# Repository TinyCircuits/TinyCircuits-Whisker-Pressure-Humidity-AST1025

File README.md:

# TinyCircuits Wireling Pressure Humidity
# AST1025 Rev2

The design files are located under design_files/ for the TinyCircuits AST1025 Rev 2 PCB. This is a Wireling board which features the Bosch BME280 Humidity, Pressure and Temperature Sensor all in one package! It measures between -40 and +85C, 0%-100% relative humidity, and from 300-1100hPa.

Format is in Cadsoft Eagle format - Eagle version 6.2 was used for the original design.

For more infomation on this, check out the product page at TinyCircuits.com

# License:

Design by TinyCircuits.
All design files are released under the Creative Commons Attribution Share-Alike 3.0 License, see the following link for details: http://creativecommons.org/licenses/by-sa/3.0

All text above must be included in any redistribution or derived design

This project uses designs and concepts developed as part of the Arduino project and the LilyPad project.  The TinyCircuits design files themselves (schematics, PCB and libraries) are not directly derived from these works' design files and have been created new, however the concepts and basic architecture behind the TinyDuino and TinyLily products are derived and we thank the hard work of the organizations below for their contributions to open-source hardware:
  
Original Arduino Uno Design by Team Arduino

LilyPad Arduino Design by Leah Buechley and Sparkfun Electronics

Please support the open-source hardware community

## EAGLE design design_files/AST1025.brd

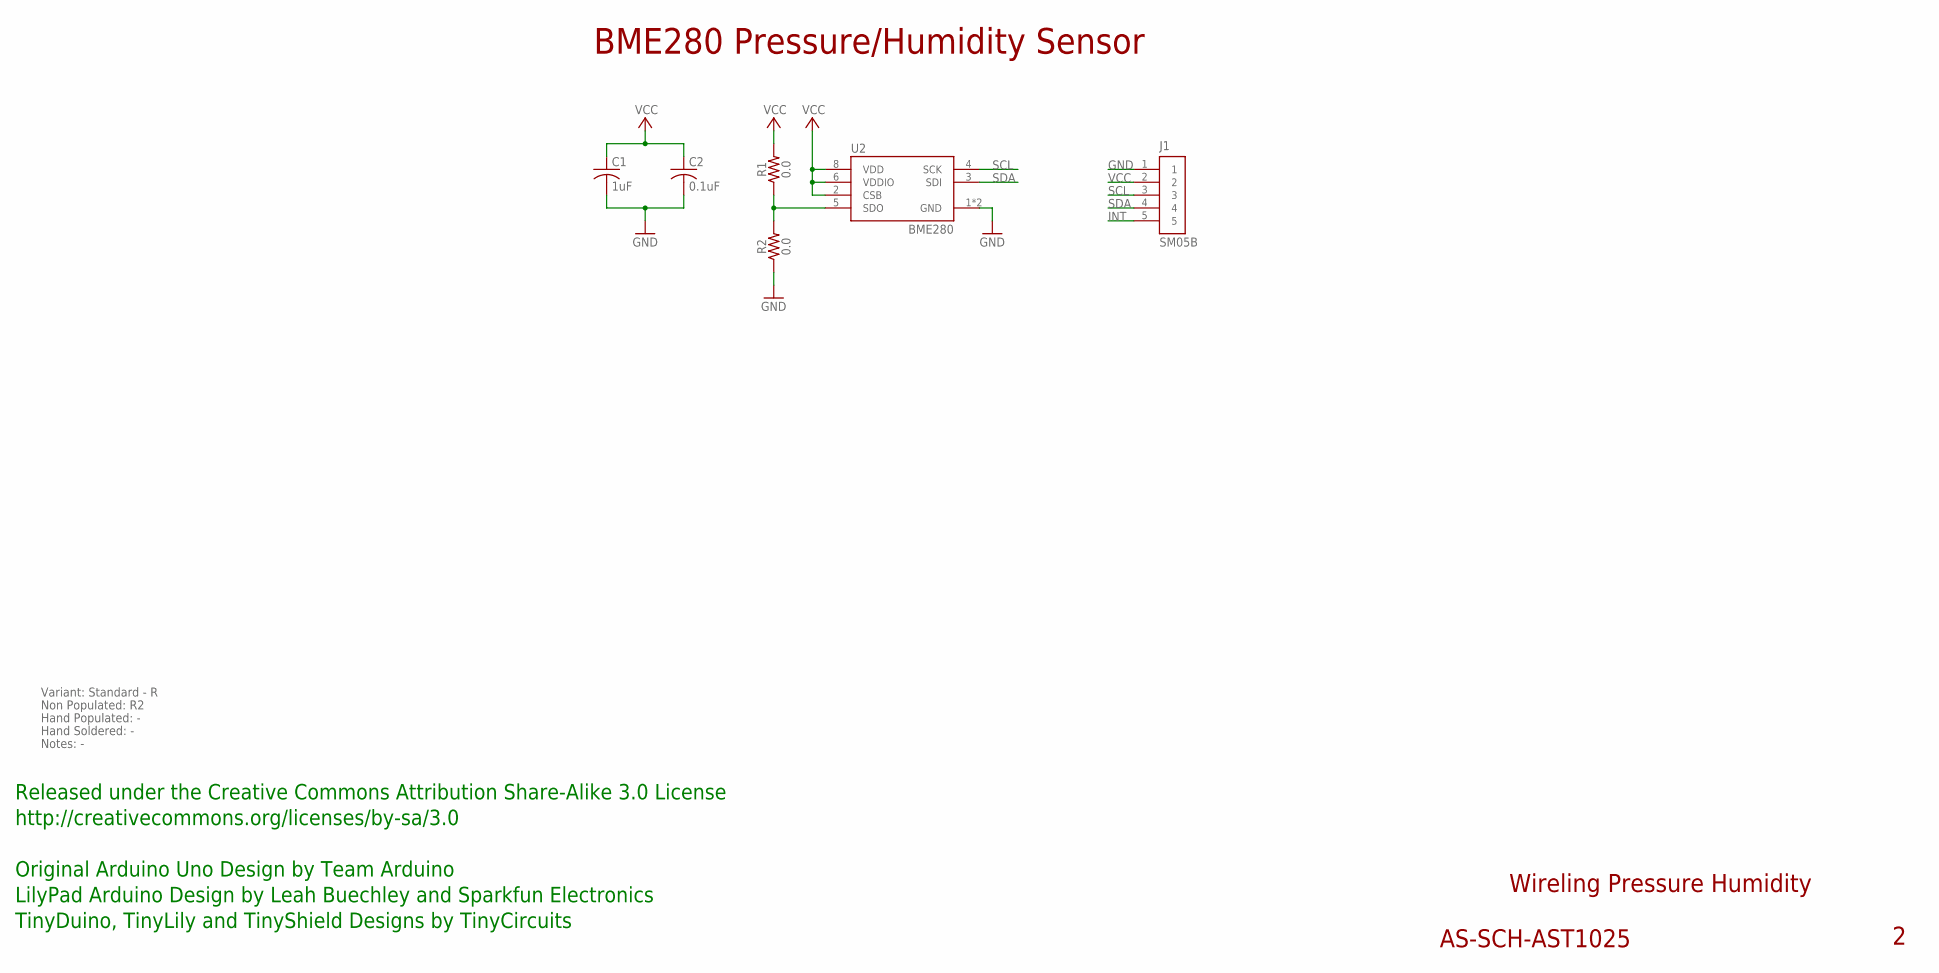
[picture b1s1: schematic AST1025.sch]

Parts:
C1: 1uF; C0603; PARTNO AS-ITM-00410
C2: 0.1uF; C0402
J1: SM05B; JST_SH_5X1_EDGE
R1: 0.0; 0402
R2: 0.0; 0402; PARTNO AS-ITM-00076
U2: BME280

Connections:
GND: C1.2, C2.2, J1.1, R2.1, U2.1 (GND), U2.7 (GND)
INT: J1.5
unnamed: R1.1, R2.2, U2.5 (SDO)
SCL: J1.3, U2.4 (SCK)
SDA: J1.4, U2.3 (SDI)
VCC: C1.1, C2.1, J1.2, R1.2, U2.2 (CSB), U2.6 (VDDIO), U2.8 (VDD)

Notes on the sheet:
Wireling Pressure Humidity
AS-SCH-AST1025
BME280 Pressure/Humidity Sensor
Released under the Creative Commons Attribution Share-Alike 3.0 License
http://creativecommons.org/licenses/by-sa/3.0
Original Arduino Uno Design by Team Arduino
TinyDuino, TinyLily and TinyShield Designs by TinyCircuits
LilyPad Arduino Design by Leah Buechley and Sparkfun Electronics
Variant: Standard - R
Non Populated: R2
Hand Populated: -
Hand Soldered: -
Notes: -

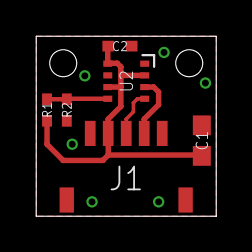
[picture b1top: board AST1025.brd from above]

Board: 2 copper layers, 10.0 x 10.0 mm, 7 parts (0 on the bottom side), 5 nets.

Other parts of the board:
U$1: DOCFIELD-TINYCIRCUITS-PCB

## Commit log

2019-07-30 updated to use Port 0
2019-08-05 added datasheet
2019-11-26 address fix
2019-12-30 updated documentation
2020-01-13 images
2020-02-04 mass image update
2020-04-16 output picture
2020-08-14 Add CAD data
2023-03-28 Add new example
